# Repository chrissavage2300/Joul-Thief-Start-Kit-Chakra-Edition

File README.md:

# Joule-Thief-Start-Kit-Chakra-Edition

This is just a starter kit I designed to be easy to solder using SMD components. Uses a ZXSC400 LED boost converter to power 7 discrete LED's that go in order: Red, Orange, Yellow, Green, Blue Green, Blue and Violet. I designed this for a friend for her birthday in the hopes that her and her bf can do something together.

 All resistors and capacitors are 1206. The main IC is an SOT23-6. It is powered by 2 AA batteries. LED current ranges from 10,15 and 20mA depending on what resistor is selected. 

Parts List:

| Part | Value | DigikeyPN |
| --- | --- | --- |
| BT1,BT2 | AA Battery Connector | BK-92-ND |
| C1,C2 | 2.2uF | 1276-1072-1-ND |
| D1 | B340A | SS16FSCT-ND |
| L1 | 22uH,1210 | 587-6397-1-ND |
| LED1 | RED | 475-1180-1-ND |
| LED2 | ORANGE | 475-2745-1-ND |
| LED3 | YELLOW | 475-2798-1-ND |
| LED4 | GREEN | 475-3119-1-ND |
| LED5 | BLUE-GREEN | 846-1188-1-ND |
| LED6 | BLUE | 754-2175-1-ND |
| LED7 | VIOLET | 754-1535-1-ND |
| Q1 | FMMT619CT | FMMT619CT-ND |
| R1 | 33mOhms | 408-1576-1-ND |
| R2 | 15Ohms | 311-15.0FRCT-ND |
| S1 | SPDT Switch | EG1903-ND |
| U1 | ZXSC400 | ZXSC400E6TACT-ND |

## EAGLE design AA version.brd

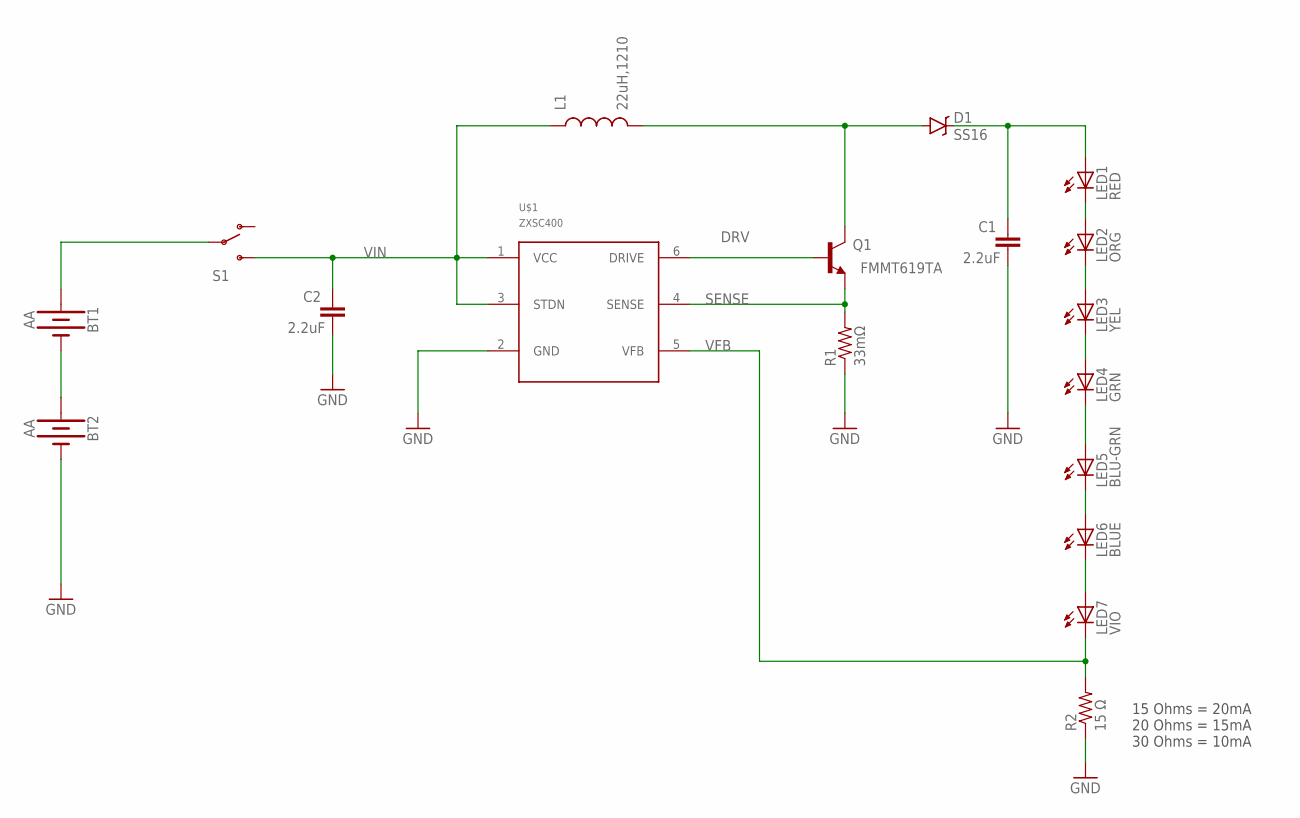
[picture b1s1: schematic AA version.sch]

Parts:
BT1, BT2: AA; BATTERY-AA
C1, C2: 2.2uF; 1206
D1: SS16; SMA-DIODE
L1: 22uH,1210; 1210
LED1: RED; P-LCC-2
LED2: ORG; P-LCC-2
LED3: YEL; P-LCC-2
LED4: GRN; P-LCC-2
LED5: BLU-GRN; P-LCC-2
LED6: BLUE; P-LCC-2
LED7: VIO; P-LCC-2
Q1: FMMT619TA; SOT23-3
R1: 33mΩ; 1206
R2: 15 Ω; 1206
S1: SWITCH-SPDTPTH_LOCK; SWITCH-SPDT_LOCK.007S
U$1: ZXSC400; SOT23-6

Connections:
DRV: Q1.1 (B), U$1.6 (DRIVE)
GND: BT2.GND@1 (-), C1.1, C2.1, R1.1, R2.1, U$1.2 (GND)
unnamed: BT1.GND@1 (-), BT2.PWR@1 (+)
unnamed: BT1.PWR@1 (+), S1.2
unnamed: D1.A, L1.2, Q1.3 (C)
unnamed: C1.2, D1.C, LED1.A
unnamed: LED1.C, LED2.A
unnamed: LED2.C, LED3.A
unnamed: LED3.C, LED4.A
unnamed: LED4.C, LED5.A
unnamed: LED5.C, LED6.A
unnamed: LED6.C, LED7.A
SENSE: Q1.2 (E), R1.2, U$1.4 (SENSE)
VFB: LED7.C, R2.2, U$1.5 (VFB)
VIN: C2.2, L1.1, S1.3 (S), U$1.1 (VCC), U$1.3 (STDN)

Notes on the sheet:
15 Ohms = 20mA 20 Ohms = 15mA 30 Ohms = 10mA

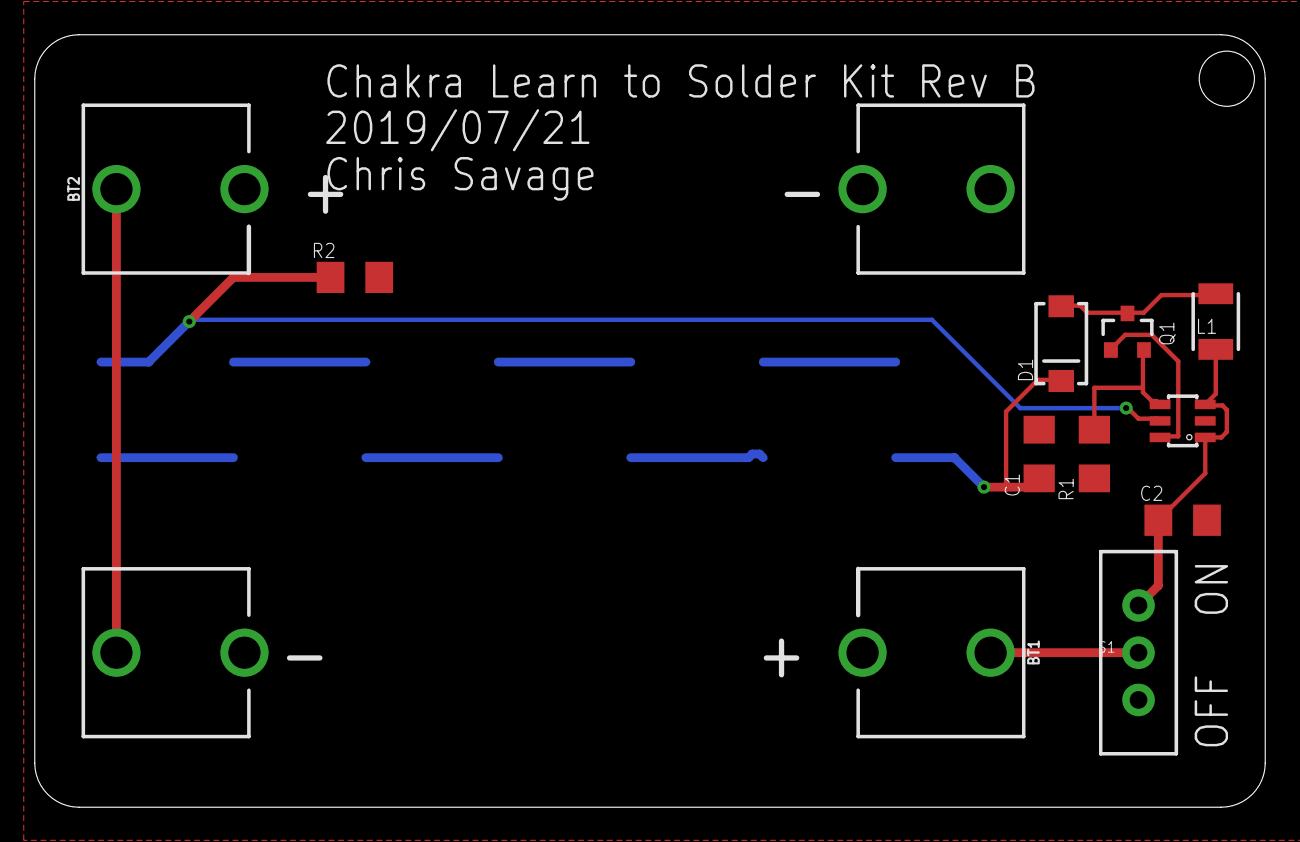
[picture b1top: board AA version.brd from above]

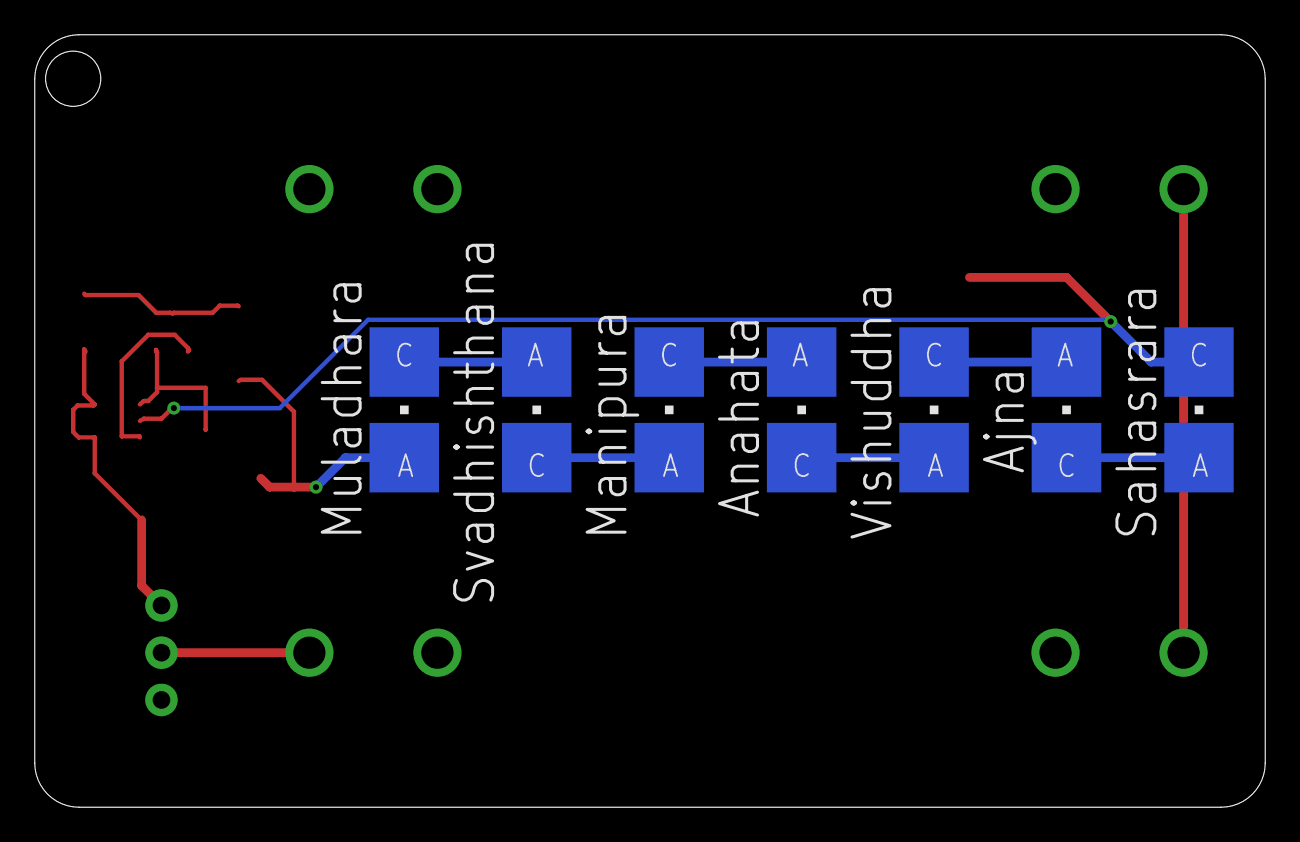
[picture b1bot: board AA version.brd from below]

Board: 2 copper layers, 70.8 x 44.4 mm, 18 parts (7 on the bottom side), 15 nets.

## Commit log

2019-08-03 Add files via upload
    8/3/2019-Board updated due to pinout error. Opps
2019-08-22 Create Photos

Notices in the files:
parts and their libraries:
SparkFun-Batteries: Licensing: Creative Commons ShareAlike 4.0 International - https://creativecommons.org/licenses/by-sa/4.0
